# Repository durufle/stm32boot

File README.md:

# STM32 Bootloader utility with scaffold v1.1

Python module to upload or download firmware to / from ST Microelectronics STM32 microcontrollers over donjon-scaffold.

## Installation

```bash
pip install ragnarok_stmloader
```
To install the latest development version

```bash
pip install git+https://github.com/durufle/stm32boot.git
```

## Usage

general usage:

```bash
Usage: python -m stm32boot [OPTIONS] COMMAND [ARGS]...

Options:
  --install-completion [bash|zsh|fish|powershell|pwsh]
                                  Install completion for the specified shell.
  --show-completion [bash|zsh|fish|powershell|pwsh]
                                  Show completion for the specified shell, to
                                  copy it or customize the installation.
  --help                          Show this message and exit.

Commands:
  devices  Devices management cli
  loader   stm32 bootloader cli
```

loader usage:

```bash
Usage: python -m stm32boot loader [OPTIONS] COMMAND1 [ARGS]... [COMMAND2
                                  [ARGS]...]...

  stm32 bootloader cli

Options:
  -p, --port TEXT        Scaffold Communication port  [default: /dev/ttyUSB0]
  -v, --verbose INTEGER  Verbosity level  [default: 5]
  --help                 Show this message and exit.

Commands:
  erase    Erase memory command
  get      Get information command
  go       Go command
  protect  protection command
  read     Read memory command
  reset    Reset to system/flash memory command
  write    Write memory command
```
devices usage:

```bash
Usage: python -m stm32boot devices [OPTIONS] COMMAND [ARGS]...

  Devices management cli

Options:
  --help  Show this message and exit.

Commands:
  add   Add device description
  list  List supported devices
```

By default, only typer is installed. You can install rich, and stm32boot show nicely formatted output.

## Reference documents
- `AN2606`: STM32 microcontroller system memory boot mode
- `AN3155`: UART protocol in the STM32 bootloader

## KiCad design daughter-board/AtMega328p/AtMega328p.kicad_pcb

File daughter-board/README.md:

# donjon-scaffold daughter boards

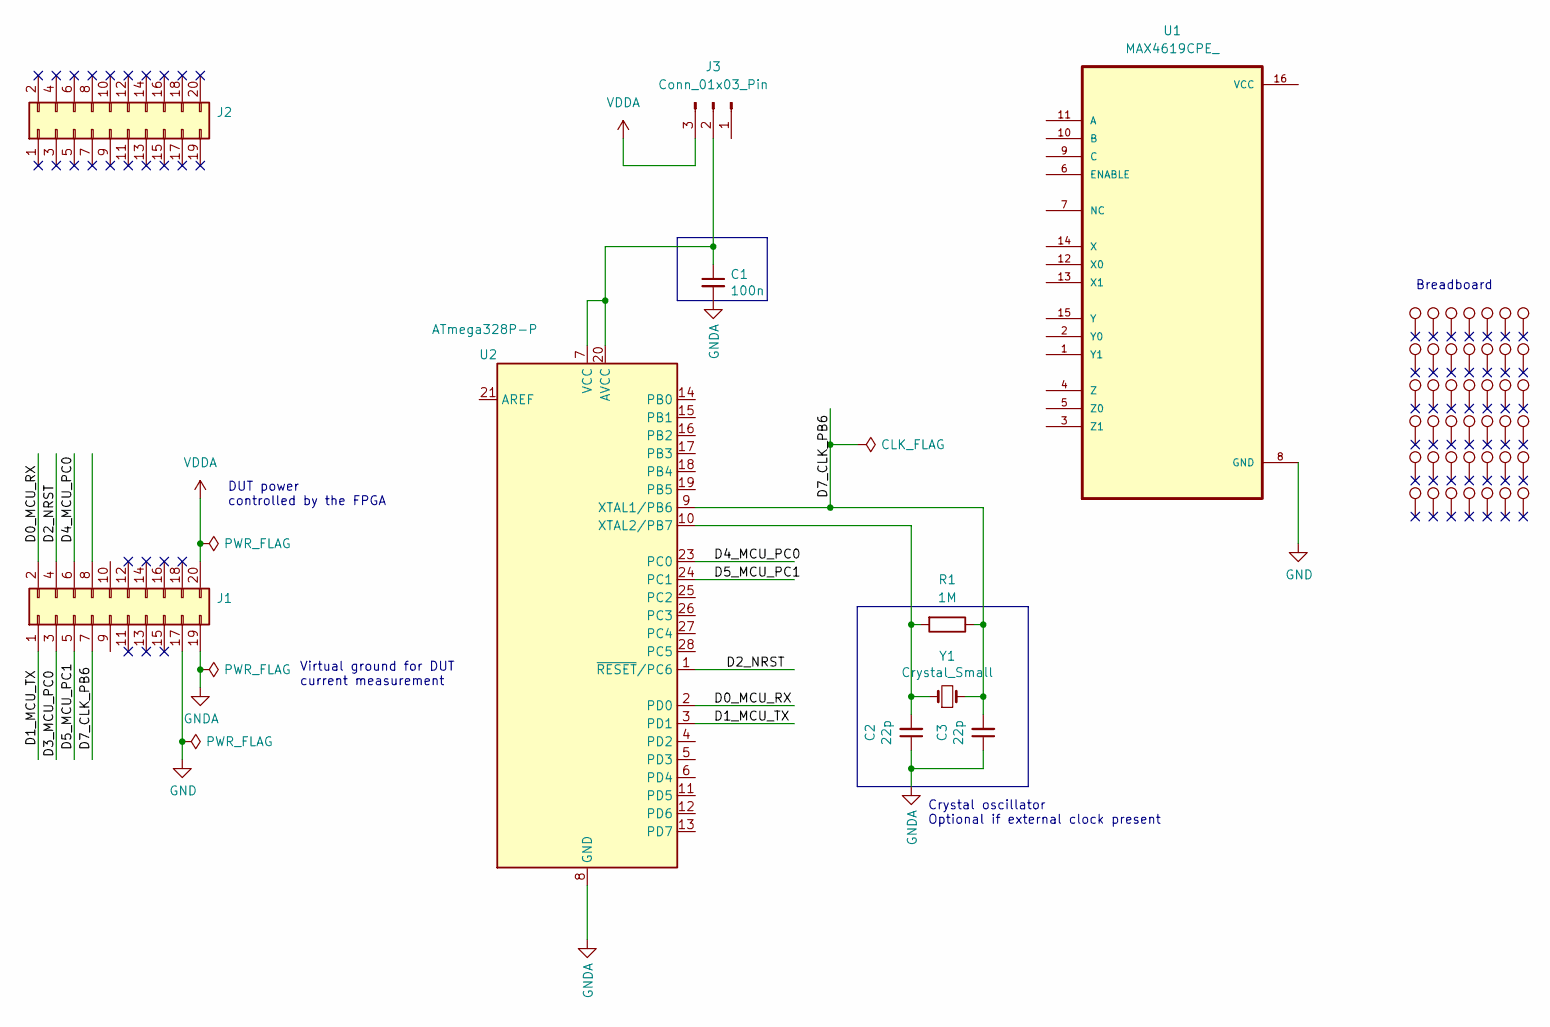
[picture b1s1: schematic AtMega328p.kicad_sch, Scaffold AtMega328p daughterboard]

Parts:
C1: 100n; C_0201_0603Metric
C2, C3: 22p; C_0805_2012Metric
J1, J2: Conn_02x10_Odd_Even; PinSocket_2x10_P2.54mm_Vertical
J3: Conn_01x03_Pin
R1: 1M; R_0402_1005Metric
TP1, TP2, TP3, TP4, TP5, TP6, TP7, TP8, TP9, TP10, TP11, TP12, TP13, TP14, TP15, TP16, TP17, TP18, TP19, TP20, TP21, TP22, TP23, TP24, TP25, TP26, TP27, TP28, TP29, TP30, TP31, TP32, TP33, TP34, TP35, TP36, TP37, TP38, TP39, TP40, TP41, TP42: TestPoint; TEST_BREADBOARD_RECTANGULAR
U1: MAX4619CPE_; DIP794W47P254L1943H457Q16
U2: ATmega328P-P; DIP-28_W7.62mm_Socket
Y1: Crystal_Small; Crystal_HC18-U_Vertical

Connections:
/D0_MCU_RX: J1.2, U2.2 (PD0)
/D1_MCU_TX: J1.1, U2.3 (PD1)
/D2_NRST: J1.4, U2.1 (~RESET/PC6)
/D3_MCU_PC0: J1.3
/D4_MCU_PC0: J1.6, U2.23 (PC0)
/D5_MCU_PC1: J1.5, U2.24 (PC1)
/D7_CLK_PB6: C3.2, J1.7, R1.1, U2.9 (XTAL1/PB6), Y1.2
GND: J1.17, U1.8 (GND)
GNDA: C1.2, C2.1, C3.1, J1.19, U2.8 (GND), U2.22 (GND)
unnamed: C1.1, J3.2, U2.7 (VCC), U2.20 (AVCC)
unnamed: C2.2, R1.2, U2.10 (XTAL2/PB7), Y1.1
VDDA: J1.20, J3.3

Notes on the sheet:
DUT power controlled by the FPGA
Crystal oscillator Optional if external clock present
Virtual ground for DUT current measurement
Breadboard

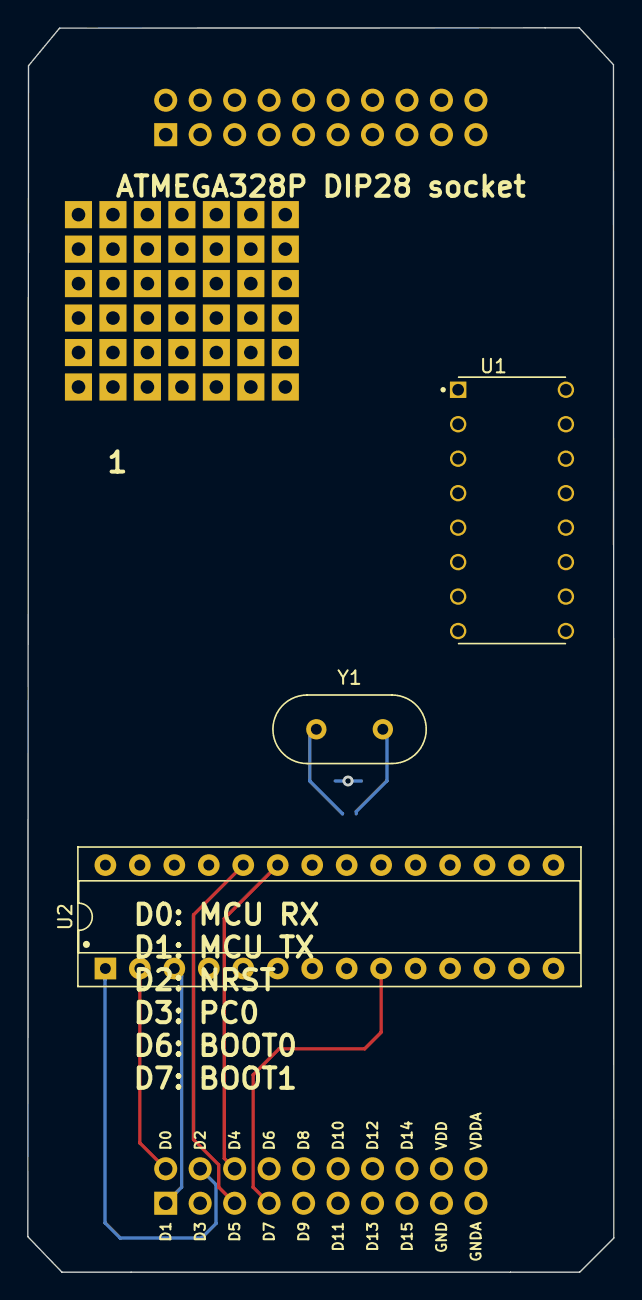
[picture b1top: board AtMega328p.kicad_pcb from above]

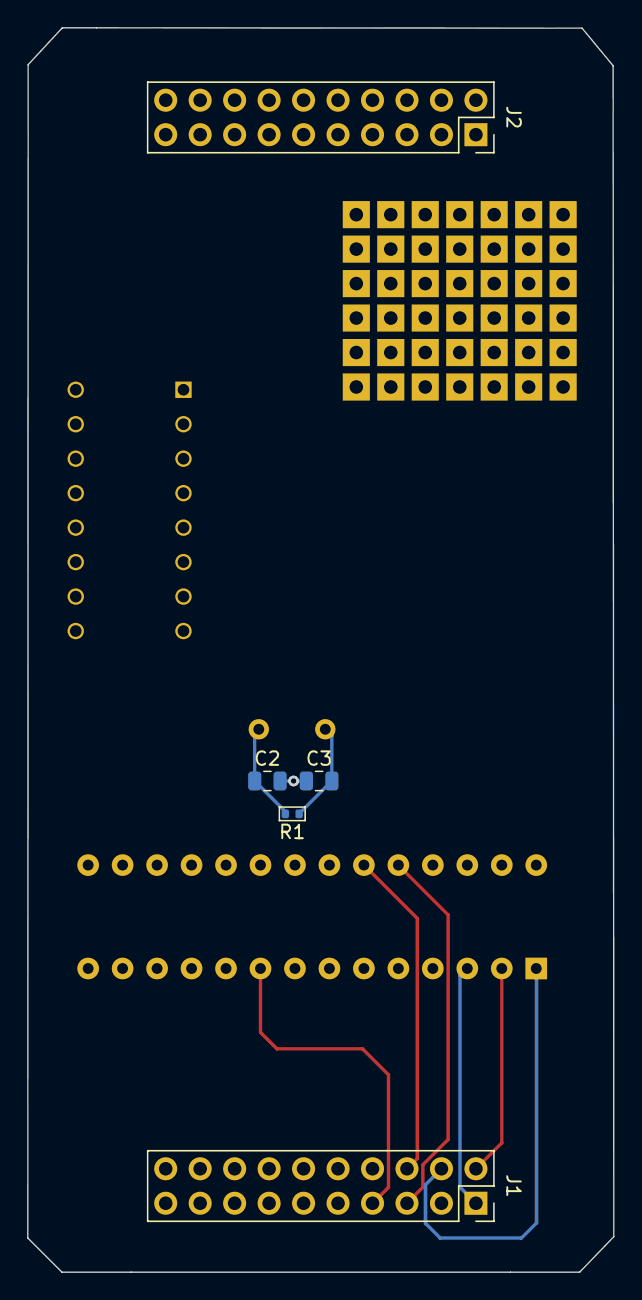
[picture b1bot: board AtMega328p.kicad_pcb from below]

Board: 2 copper layers, 43.2 x 91.7 mm, 50 parts (5 on the bottom side), 10 nets.

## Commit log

2024-02-17 Change structure - update project files
2024-02-18 Correction on sys.argv usage
2024-02-18 Update pylint.yml
    Add dependencies
2024-02-18 Update comment
2024-02-18 minor correction
2024-02-18 Update according to pylint
2024-02-19 Add sphinx project and daughter board directory
2024-02-19 Update pylint.yml
    Change due to Node.js warning
2024-02-19 Update pylint.yml
    Indicate branch name (main)
2024-02-22 Add firmware and its python script
2024-02-22 Scaffold intenciated in the class
2024-02-22 Add stm32l476 daughter board
2024-02-22 Add uart trigger support
2024-02-23 Uddate board design
2024-02-25 Usage of typer package for CLI application
2024-02-27 pylint: update and correction - pytest: add cli parameters test
2024-02-27 Update REDAME
2024-02-27 Remove test script from pylint scanning
2024-02-27 Remove test script from pylint scanning: typo
2024-02-27 Add type in depencies for pylint
2024-02-27 Add requirements file
2024-02-27 Add test action script
2024-02-27 Set tests as package - change main to entry
2024-02-28 Update cli arguments testing
2024-02-28 try catch on int validation callback
2024-02-28 excludes more dircetory from build package
2024-02-28 pylint: corretion
2024-02-28 Update github action for test
2024-02-28 Update python-app script for testing
2024-02-28 Update python-app script: correction
2024-02-28 Add flake8 configuration file
2024-02-28 Test github self runner
2024-02-29 INstall by default only typer package - Add short args/option - Add test
2024-02-29 Add python 3.11 for test
2024-02-29 Add try catch during reset command
2024-02-29 versioning: start bump version script
2024-02-29 versioning: correction on versioning configuration
2024-03-01 Change package and cli application name
2024-03-05 Major update: Add device description file - split cli (loader/devices) - Add test
2024-03-05 Update daughter board
2024-03-05 Change file header - pylint error correction
2024-03-05 pylint error in script : add missing package
2024-03-06 Bootloader protocol version and Bootloader Id - Add fields in schema
2024-03-06 Update flash page size for Id 0x462
2024-03-06 pytest data file update according to schema
2024-03-07 Change package folder name - Add integration test and actions script
2024-03-07 Change integration script name
2024-03-07 Remove integration scri add workflow_dispatch in test python application
2024-03-07 exclude integration script in CI
2024-03-25 Bug correction (erase command)- Add external clock generation on ceval test script
2024-03-27 Add gooey support for ceval script - Add documentation
2024-03-27 Create python-app-int.yml
    Application integration test
2024-03-27 Update python-app-int.yml
    Add self hosted runner
2024-03-27 Update runs-on
2024-03-27 remove integration workflow
2024-03-27 Update github workflow
2024-03-27 Update integration workflow
2024-03-27 Update pyproject: add pytest option for coverage
2024-03-27 Update pyproject: correction on script path
2024-03-27 Update unit test workflow: Sava data as artifact
2024-03-27 Update unit test workflow: correction
2024-03-27 Update pyproject: Add coverage path
2024-03-27 Update unit workflow: select test
2024-03-27 Update workflows: Change name and add artifact in integration test
2024-03-27 Add unit/int for test name
2024-03-27 Correction made un pytest run
2024-03-27 Add docstring missin
2024-03-27 Add docstring missing in test
2024-03-27 Perfom all test in integration
2024-03-29 Add a test firmware for stm32l462 target
2024-03-31 Update documentation
2024-03-31 Change sphinx theme and add logo
2024-03-31 Update doc
2024-04-01 Update README.md
    Add badge
2024-04-01 Update README.md
    Add lable lint to badge
2024-04-01 Update README.md
    Add unitary test badge
2024-04-01 Update README.md
    typo
2024-04-08 Update after merge
2024-04-08 Update readthedocs script
2024-04-09 Update documentation and add examples
2024-04-09 Add examples
2024-04-14 Update documentations
2024-04-14 Update sphinx documentations files
2024-04-16 l462 routing - Add ATMega board - Update ceval script
2024-04-29 Update atmega board

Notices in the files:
daughter-board/AtMega328p/AtMega328p.kicad_pcb:
Under LGPL v3 license
